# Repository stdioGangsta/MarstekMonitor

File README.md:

# MarstekMonitor

Small device with integrated display to monitor Marstek Venus battery systems.

Works on the 5.12kWh and 2.56kWh Marstek Venus battery.

Thanks to Superduper1969 and Tweakers (in Dutch) for EPSHome config and Modbus communication.

https://gathering.tweakers.net/forum/list_messages/2282240/0

WARNING:
Marstek has different versions of the Venus battery systems. The pinout of the RS485 connector is slightly different.
Currently, MarstekMonitor only supports Gen1 out of the box. Future versions will support all currently known models.

## Main features
-Plugs directly into the RS485 port on the side of the battery

-Easy configuration via ESPHome (and connection to Home Assistant)

-Display shows:

Battery Operating Mode (Idle, Charge, Discharge)

Charge/Discharge power

Battery SoC (State of Charge)

Charging Strategy (Auto, AI, Custom)

-No separate power supply needed

-(optional) Can be connected to WiFi to monitor/control the battery remotely (eg. Home Assisstant)\
The device is fully functional without a WiFi connection.

## What's in this repository?
#### Enclosure
Drawing of enclosure for the MarstekMonitor (behuizing) ( Both FreeCAD 0.21 and ready-to-3D-print .STL files)

#### HW
KiCAD 9.0 schematic and board files, including footprints for the used modules
#### SW
ESPHome yaml file

## HW v0.1
HW v0.1 is meant to be a proof of concept only. It consists of nothing more than a carrier board for the various modules.

09-04-2025: v0.1 assembled and working! There are a few minor issues that will be solved in the next version. See below.

Partlist:
1. MarstekMonitor v0.1 PCB 
2. LilyGo ESP32 T-Display v1.1 [link](https://www.tinytronics.nl/en/development-boards/microcontroller-boards/with-wi-fi/lilygo-ttgo-t-display-v1.1-esp32-with-1.14-inch-tft-display "Webshop").
3. Buck-Boost converter [link](https://www.tinytronics.nl/en/power/voltage-converters/buck-boost-(step-up-down)-converters/dc-dc-step-up-down-buck-boost-converter-0.6a-5v-output "Webshop").
4. RS485-Serial module [link](https://nl.aliexpress.com/item/1005008217845791.html)
5. 3d Printed enclosure 
6. RS485 Connector: Weipu SP17, 5pin male connector. This connector is supplied with the Marstek battery

### Known issues with HW v0.1
These will be solved in the next HW iteration
1. GPIO12 used for RS485. GPIO12 is an ESP32 strapping pin. This can cause issues on reset.
2. Switch to right-angle JST-XH connector
3. Footprint for Buck-boost and RS485 module: TH diameter slighty too small. Modules fit, but need to be forced in.
4. Silkscreen for Lilygo T-display does not match actual footprint
5. Panel mount Weipu 6p connector does not seem to exist.

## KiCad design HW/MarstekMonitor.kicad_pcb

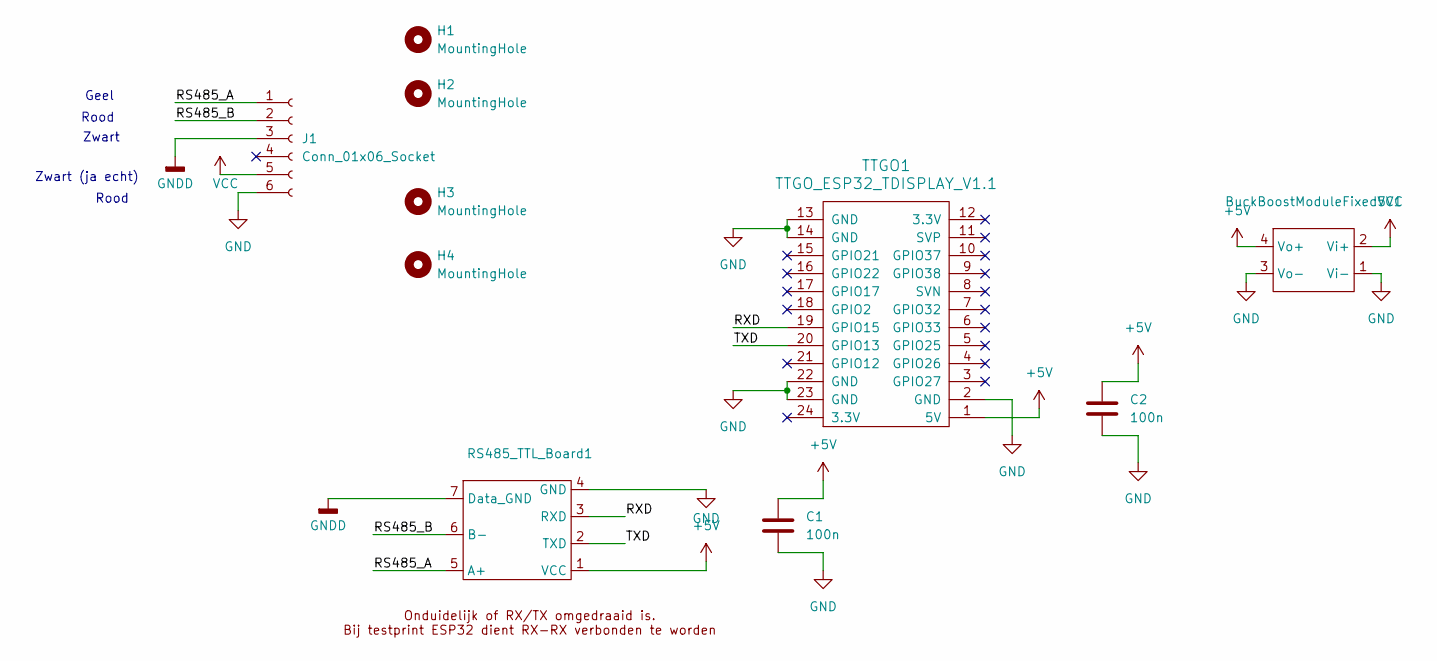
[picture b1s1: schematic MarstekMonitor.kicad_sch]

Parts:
BuckBoostModuleFixed5V1: buckboostmodule5V
C1, C2: 100n; C_1210_3225Metric_Pad1.33x2.70mm_HandSolder
H1, H2, H3, H4: MountingHole; MountingHole_3.2mm_M3
J1: Conn_01x06_Socket; JST_XH_B6B-XH-AM_1x06_P2.50mm_Vertical
RS485_TTL_Board1: RS485-TTL_module
TTGO1: TTGO_ESP32_TDISPLAY_V1.1; TTGO_ESP32_TDisplay_v1.1

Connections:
+5V: BuckBoostModuleFixed5V1.4 (Vo+), C1.1, C2.1, RS485_TTL_Board1.1 (VCC), TTGO1.1 (5V)
/RS485_A: J1.1, RS485_TTL_Board1.5 (A+)
/RS485_B: J1.2, RS485_TTL_Board1.6 (B-)
/RXD: RS485_TTL_Board1.3 (RXD), TTGO1.19 (GPIO15)
/TXD: RS485_TTL_Board1.2 (TXD), TTGO1.20 (GPIO13)
GND: BuckBoostModuleFixed5V1.1 (Vi-), BuckBoostModuleFixed5V1.3 (Vo-), C1.2, C2.2, J1.6, RS485_TTL_Board1.4 (GND), TTGO1.2 (GND), TTGO1.13 (GND), TTGO1.14 (GND), TTGO1.22 (GND), TTGO1.23 (GND)
GNDD: J1.3, RS485_TTL_Board1.7 (Data_GND)
VCC: BuckBoostModuleFixed5V1.2 (Vi+), J1.5

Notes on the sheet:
Rood
Geel
Zwart (ja echt)
Zwart

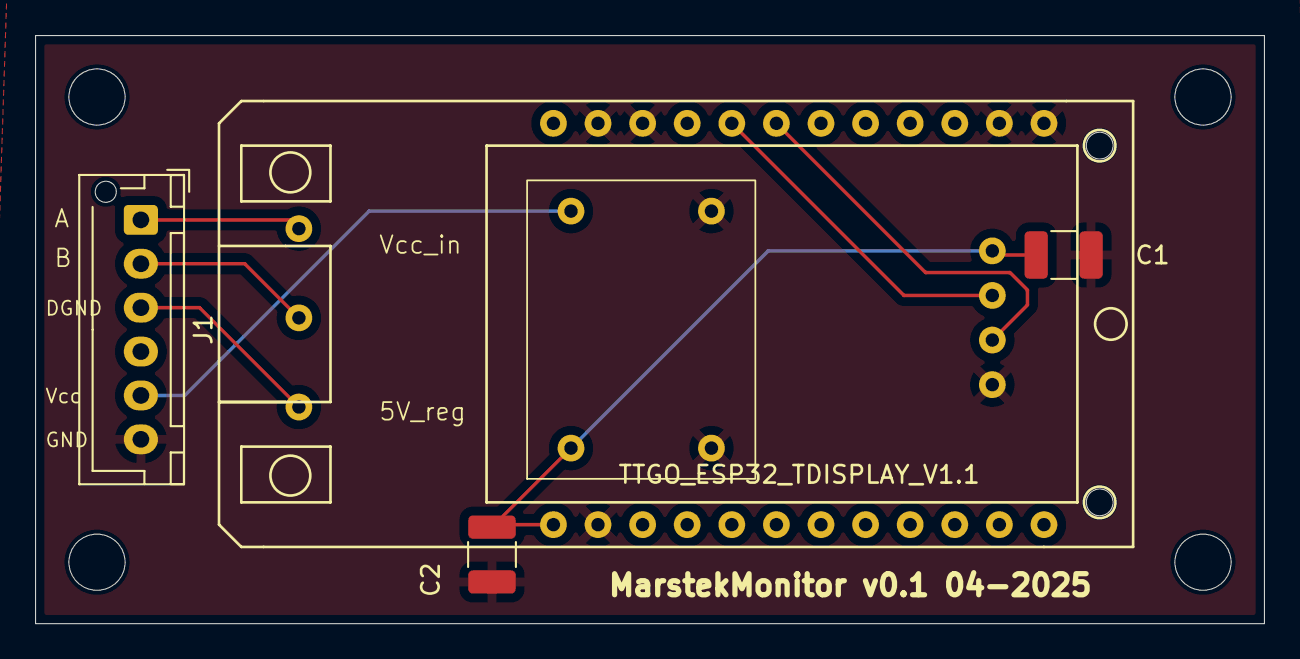
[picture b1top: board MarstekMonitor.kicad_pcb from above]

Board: 2 copper layers, 70.0 x 33.5 mm, 10 parts (1 on the bottom side), 8 nets.

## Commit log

2025-03-03 Update lilygo-rs485.yaml
    Added Binary Sensors
2025-03-05 Update lilygo-rs485.yaml
    Change update rate Power
2025-04-02 Initial commit for PoC.
    Includes ESPHome yaml and Kicad 9.0 design files for first version of carrier board
2025-04-10 Enclosure v0.1
2025-04-10 Add Releases folder
2025-04-10 Added top to enclosure.
2025-04-11 Readme
2025-04-17 Enclosure updated
    Enclosure made smaller (lower, shorter).
2025-04-23 PCB layout updated
    Fixed wrong GPIO pin for RX
2025-05-09 Marstek Venus different versions
